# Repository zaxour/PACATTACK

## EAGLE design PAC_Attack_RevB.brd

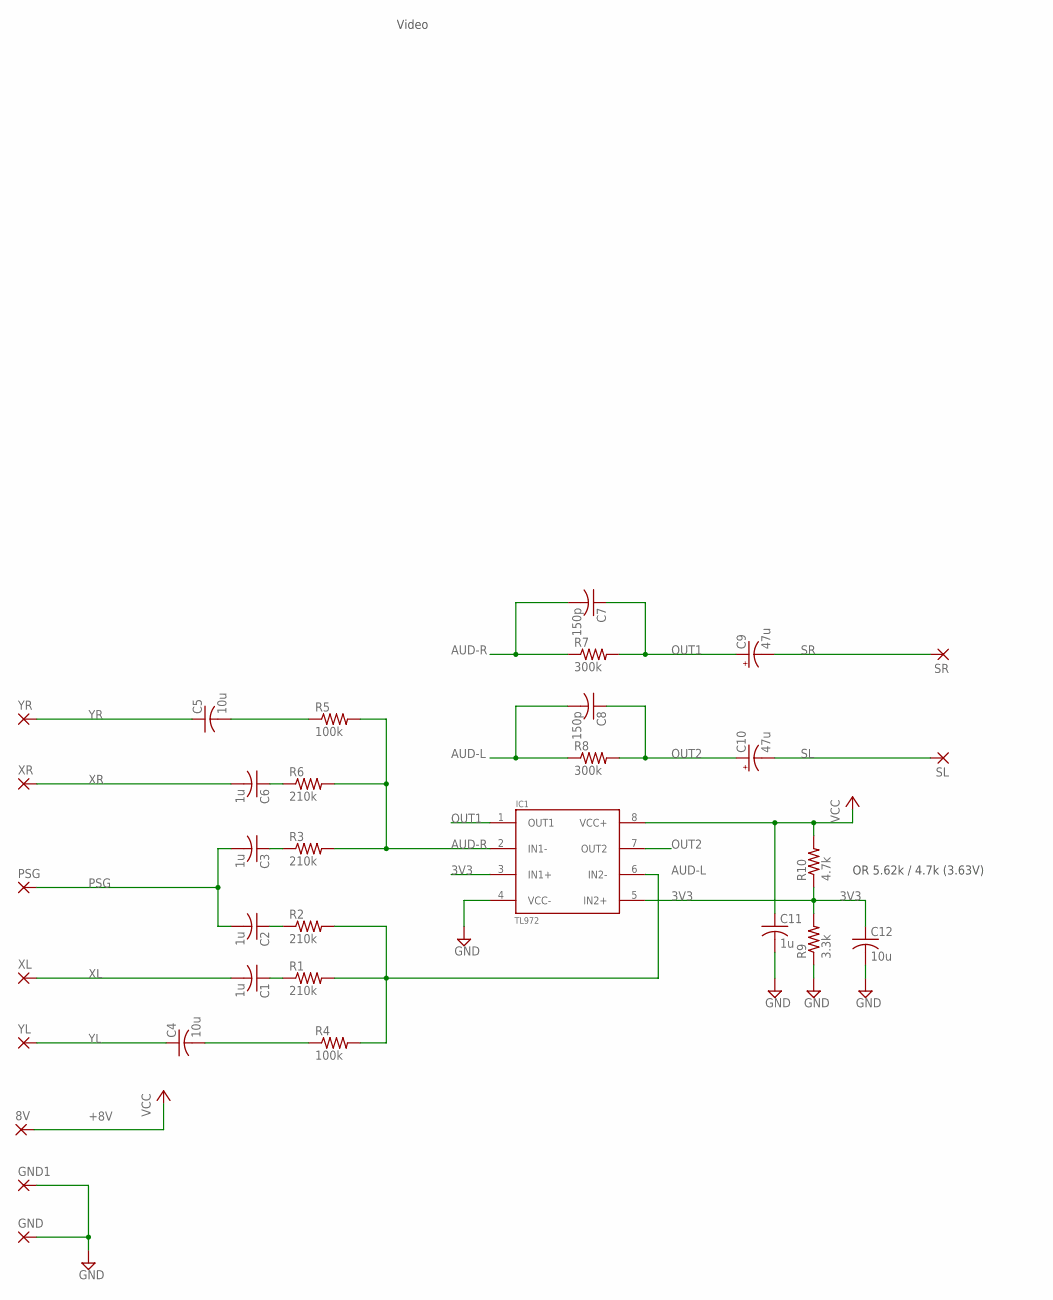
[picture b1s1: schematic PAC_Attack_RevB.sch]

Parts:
8V: SMD2; SMD1,27-2,54
C1, C2, C3, C6, C11: 1u; C0603
C4, C5: 10u; C0805
C7, C8: 150p; C0603
C9, C10: 47u; CT3528
C12: 10u; C1206
GND, GND1: SMD2; SMD1,27-2,54
IC1: TL972; SOIC8
PSG: SMD2; SMD1,27-2,54
R1, R2, R3, R6: 210k; R0603
R4, R5: 100k; R0603
R7, R8: 300k; R0603
R9: 3.3k; R0603
R10: 4.7k; R0603
SL: SMD2; SMD1,27-2,54
SR: SMD2; SMD1,27-2,54
XL: SMD2; SMD1,27-2,54
XR: SMD2; SMD1,27-2,54
YL: SMD2; SMD1,27-2,54
YR: SMD2; SMD1,27-2,54

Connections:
3V3: C12.1, IC1.3 (IN1+), IC1.5 (IN2+), R9.2, R10.1
+8V: 8V.1, C11.1, IC1.8 (VCC+), R10.2
AUD-L: C8.2, IC1.6 (IN2-), R1.2, R2.2, R4.2, R8.1
AUD-R: C7.2, IC1.2 (IN1-), R3.2, R5.2, R6.2, R7.1
GND: C11.2, C12.2, GND.1, GND1.1, IC1.4 (VCC-), R9.1
unnamed: C5.2, R5.1
unnamed: C4.2, R4.1
unnamed: C6.1, R6.1
unnamed: C3.1, R3.1
unnamed: C2.1, R2.1
unnamed: C1.1, R1.1
OUT1: C7.1, C9.+, IC1.1 (OUT1), R7.2
OUT2: C8.1, C10.+, IC1.7 (OUT2), R8.2
PSG: C2.2, C3.2, PSG.1
SL: C10.-, SL.1
SR: C9.-, SR.1
XL: C1.2, XL.1
XR: C6.2, XR.1
YL: C4.1, YL.1
YR: C5.1, YR.1

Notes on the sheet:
Video
OR 5.62k / 4.7k (3.63V)

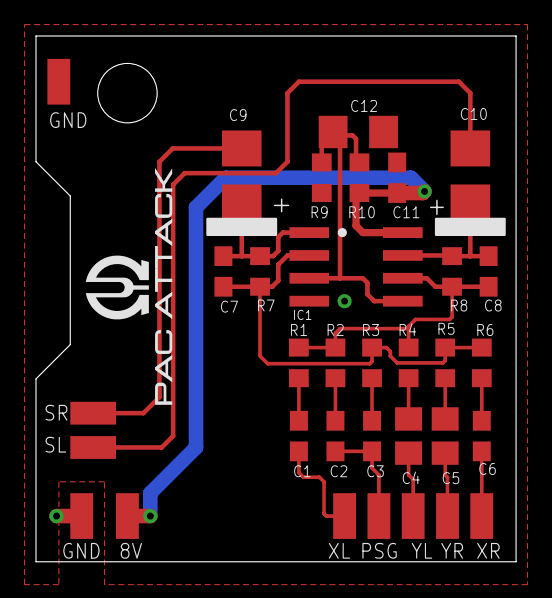
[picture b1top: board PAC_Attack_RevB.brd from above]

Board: 2 copper layers, 26.7 x 29.2 mm, 33 parts (0 on the bottom side), 20 nets.

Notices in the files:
PAC_Attack_RevB.brd:
Licensed under
CERN OHL v1.2
